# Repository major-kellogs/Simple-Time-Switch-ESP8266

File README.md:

# Simple-Time-Switch-ESP8266 #

## Description ##
This is a simple time switch made with an ESP8266 (board: ESP01S). It is originally made for a small LED panel. But of course you can use it as you wish.

## Features ##
-  With the used hardware it is possible to switch an 12 volts output.
-  WIFI is used to set the current time of the microcontroller.

## Getting started ##
-  Import the project into the ide of your choice (CLion by Jetbrains is recommended) and make sure that you are using [PlatformIO](https://platformio.org/) as plugin.
### Adjust the time to switch ###
To adjust the time when the switch events should happen you need to modify the following code block  inside the function `void controlLEDs()` of the file **src->main.cpp** beginning at line 42.
```C++
uint8 isLEDBright =
        (timeInfo.tm_hour >= 10 && timeInfo.tm_hour < 15) ||
        (timeInfo.tm_hour >= 18 && timeInfo.tm_hour < 23);
```
As you can see, this code switches the output between **10:00am and 03:00pm** as well as between **06:00pm and 11:00pm** to `HIGH`.

### Get WIFI connectivity ###
The ESP8266 chip is only capable to connect to a 2.4 GHz WIFI. To get it working you simply need to insert your WIFI credentials inside the file **src->credentials.h**
```C++
const char *ssid = "YOUR SSID";
const char *password = "YOUR PASSPHRASE";
```
### Needed Components ###
-  pcb prototyping board with a grid of at least 20x6 (2,54mm)
-  ESP-01S microcontroller
-  12v LED panel or what ever you want to switch on and off (check the datasheets of the BC337 transistor and the LD1117AV33 Voltage regulator for the max current)
-  transistor BC337
-  Voltage regulator LD1117AV33 
-  resistor 2K2
-  resistor 10K
-  capacitor 100nF
-  capacitor 22µF
-  some wires and solder
-  appropriate 12v power source

Check **circuit-overview.png** for the correct wiring.

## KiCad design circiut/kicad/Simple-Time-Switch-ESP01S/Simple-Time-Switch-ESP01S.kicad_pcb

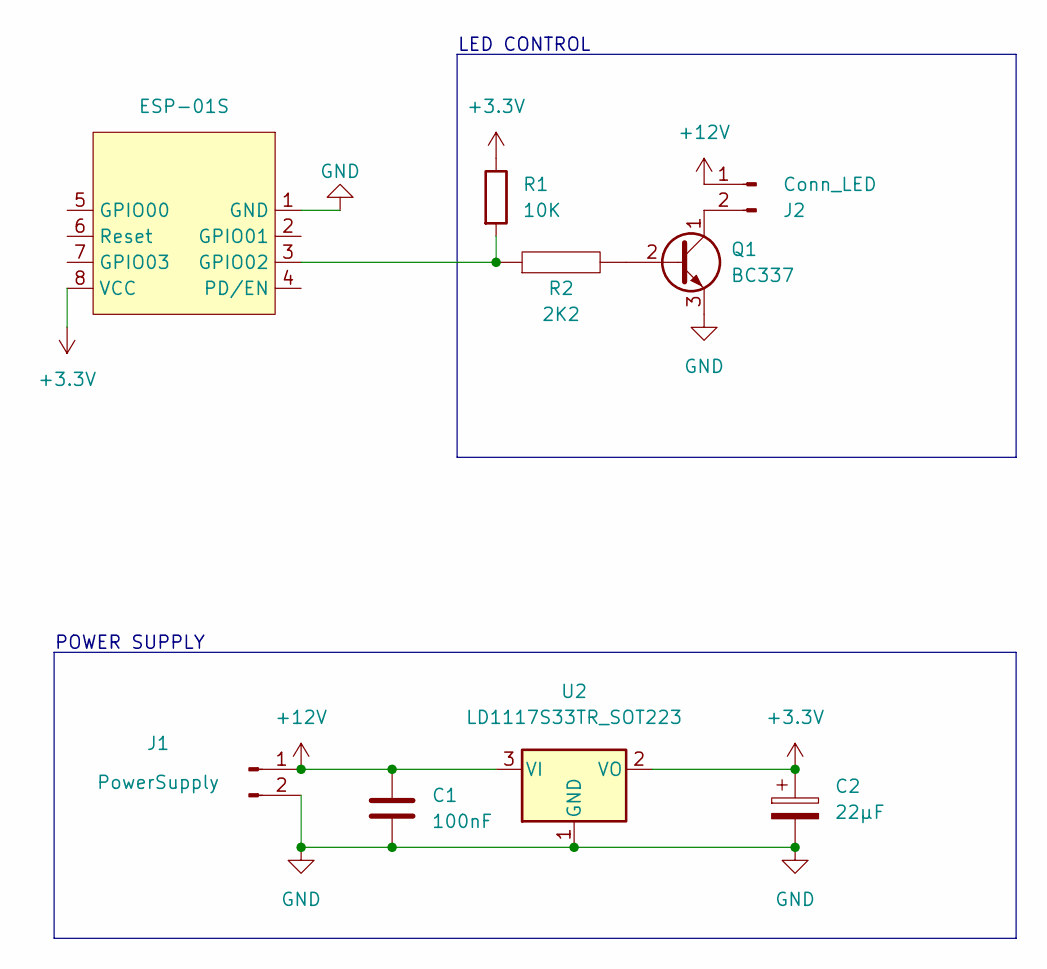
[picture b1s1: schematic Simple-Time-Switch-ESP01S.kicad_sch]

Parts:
C1: 100nF; PinHeader_1x02_P2.54mm_Vertical
C2: 22µF; PinHeader_1x02_P2.54mm_Vertical
J1: PowerSupply; PinHeader_1x02_P2.54mm_Vertical
J2: Conn_LED; PinHeader_1x02_P2.54mm_Vertical
Q1: BC337; FanPinHeader_1x03_P2.54mm_Vertical
R1: 10K; R_Axial_DIN0207_L6.3mm_D2.5mm_P10.16mm_Horizontal
R2: 2K2; R_Axial_DIN0207_L6.3mm_D2.5mm_P10.16mm_Horizontal
U1: ESP-01S; ESP_01S
U2: LD1117S33TR_SOT223; TO-220F-3_Vertical

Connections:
+3V3: C2.1, R1.1, U1.8 (VCC), U2.2 (VO)
+12V: C1.1, J1.1, J2.1, U2.3 (VI)
GND: C1.2, C2.2, J1.2, Q1.3 (E), U1.1 (GND), U2.1 (GND)
unnamed: J2.2, Q1.1 (C)
unnamed: Q1.2 (B), R2.2
unnamed: R1.2, R2.1, U1.3 (GPIO02)

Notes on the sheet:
LED CONTROL
POWER SUPPLY

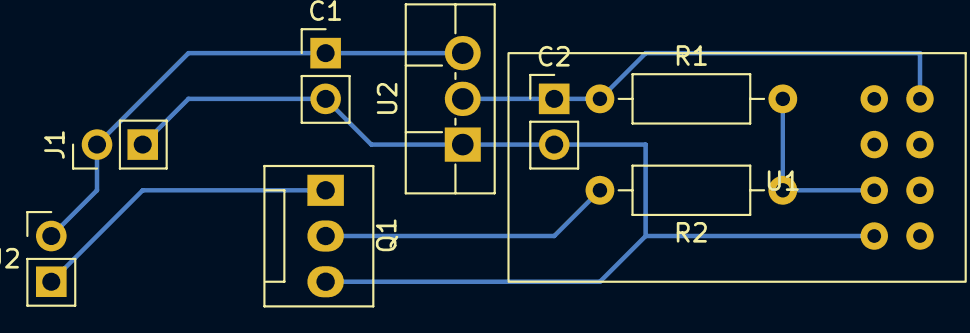
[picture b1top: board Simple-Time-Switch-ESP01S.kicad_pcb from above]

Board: 2 copper layers, 9 parts (0 on the bottom side), 6 nets.

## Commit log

2023-03-06 enhances readme
